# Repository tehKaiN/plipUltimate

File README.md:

# plipUltimate
plipUltimate is AVR-based device used to connect classic Amigas via Ethernet to the network. Additionally, it serves as SD card reader and includes self-updater. This project is based on [PlipBox](https://github.com/cnvogelg/plipbox).

Released under the GNU Public License V2 (see LICENSE and AUTHORS for details).

Currently IP traffic is done in bridge mode - packets are generated by Amiga's network stack and sent to interface using PLIP protocol. Since AVR CPU may run as fast as 20MHz, there is a room for improvement by moving generic packet generation to AVR. SD card reader support is yet to be added.

Both projects are released under GPLv2 license.

## Releases

See [Releases page](https://github.com/tehKaiN/plipUltimate/releases).

**Read `release notes.txt` included in release before doing anything else, otherwise you may end up very frustrated with broken pile of electronics.**

All releases consists of:

- KiCad project files: use these to generate your own gerbers,
- Gerber files: use these to order PCB from fab house,
- `amiga-sw` folder containing all prebuilt Amiga software,
- `avr-bin` folder containing prebuilt AVR .hex file,
- `changelog.txt` listing changes between releases,
- `release notes.txt` file containing important notes regarding current release.

## Assembling device

Unlike PlipBox, this project uses it's own custom PCB. Because of track pitches and vias, it is strongly advised to send Gerbers to board house.

After assembling device, you will need to program AVR with attached .hex file using on-board ISP header. Use programmer of your choice. I tend to use cheap Arduino clone as programmer (see [ArduinoISP](https://www.arduino.cc/en/Tutorial/ArduinoISP)). 

Flashing from release is done as follows:  
```
avrdude -V -p m328p -c arduino -b 19200 -PCOM3 -Uflash:w:"avr-bin\plipUltimate.hex":i -Uflash:w:"avr-bin\avr-bootloader.hex":i -Ueeprom:w:"avr-bin\plipUltimate.eep":i -U lfuse:w:"avr-bin\plipUltimate.lfs":i -U hfuse:w:"avr-bin\plipUltimate.hfs":i -U efuse:w:"avr-bin\plipUltimate.efs":i -U lock:w:"avr-bin\plipUltimate.lock":i
```
Whereas from repository:  
```
avrdude -V -p m328p -c arduino -b 19200 -PCOM3 -Uflash:w:"avr\bin\Debug\plipUltimate.hex":i -Uflash:w:"avr-bootloader\bin\Debug\avr-bootloader.hex":i -Ueeprom:w:"avr\bin\Debug\plipUltimate.eep":i -U lfuse:w:"avr\bin\Debug\plipUltimate.lfs":i -U hfuse:w:"avr\bin\Debug\plipUltimate.hfs":i -U efuse:w:"avr\bin\Debug\plipUltimate.efs":i -U lock:w:"avr\bin\Debug\plipUltimate.lock":i
```
Where `-c arduino` is your ISP type and `-PCOM3` is your ISP's COM port.

## Amiga configuration

Since Amiga software is still same as in plipBox, it's configuration steps are exactly the same. You can find details [here](https://github.com/cnvogelg/plipbox/blob/master/doc/src/amiga.md).

## Updates

plipUltimate may be updated using plipTool. Internet service providing latest update files is yet to be established.

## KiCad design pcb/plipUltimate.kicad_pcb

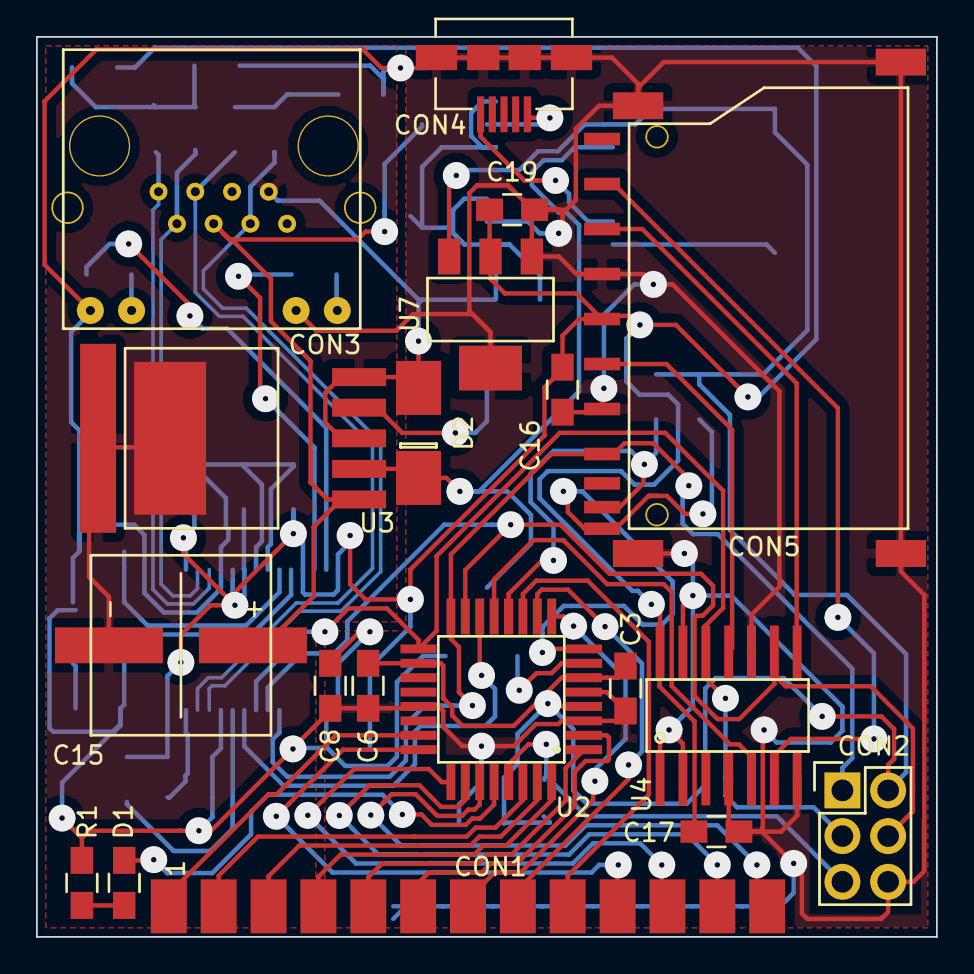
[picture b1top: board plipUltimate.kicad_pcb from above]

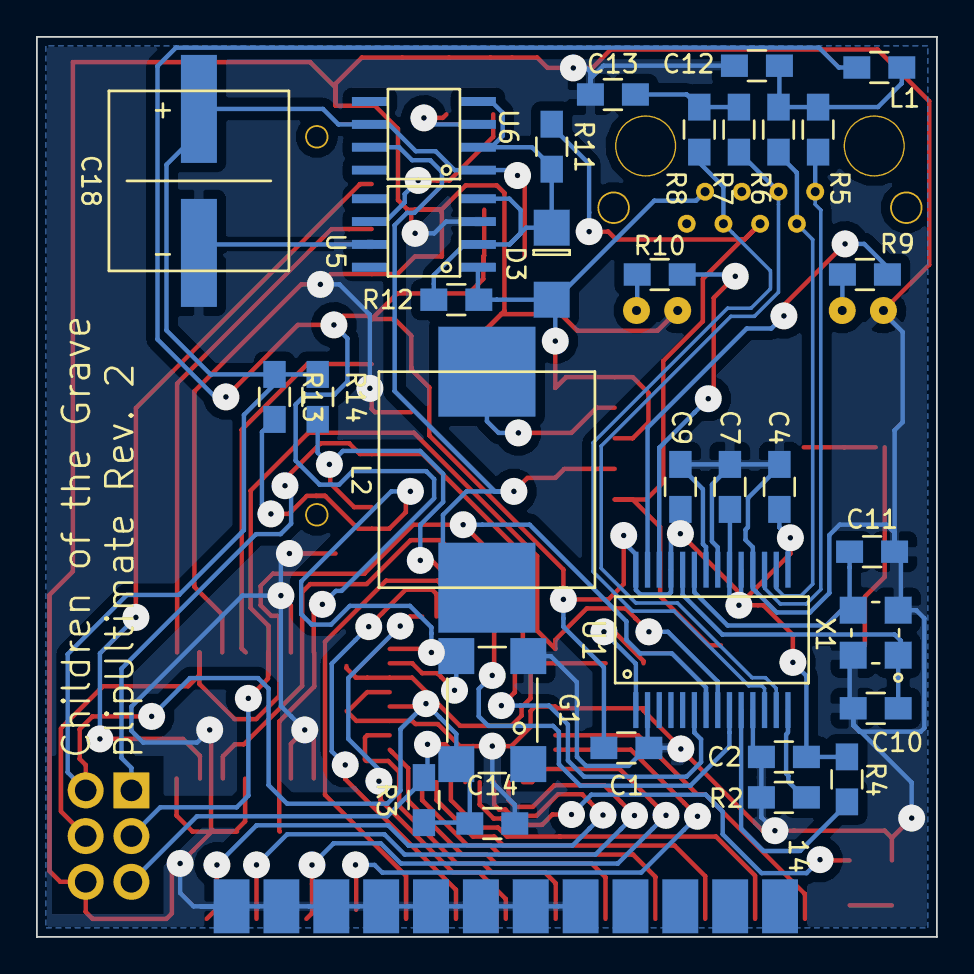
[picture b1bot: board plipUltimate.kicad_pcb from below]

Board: 2 copper layers, 50.0 x 50.0 mm, 51 parts (32 on the bottom side), 52 nets.

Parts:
C1, C2, C3, C4, C6, C7, C9, C14, C16: 100nF; 0805
C8: 10uF; 0805
C10, C11: 18pF; 0805
C12, C13, C17: 10nF; 0805
C15: 100uF 50V loESR; electrolyte_SMD
C18: 220uF 35V loESR; electrolyte_SMD
C19: 10uF 6,3V; 0805
CON1: IEEEE-1284A; d-sub25_edge
CON2: AVR-ISP-6; IDC_2x3
CON3: RJ45_C; RJ45-LEDS
CON4: USB_microB; USB-MicroB
CON5: SD_SPI; SD-SHORT
D1: YEL_LED; 0805
D2: SS34; SMA
D3: BZV55C10; SOD-80
G1: CFPS-72-20M; SMD_7050
L1: FB 100mA; 0805
L2: DE1207-100; DE-1207
R1: 820R; 0805
R2: 2k7 1%; 0805
R3, R4, R12: 10k; 0805
R5, R6, R7, R8: 49R9 1%; 0805
R9, R10: 270R; 0805
R11: 22k; 0805
R13, R14: 4k7; 0805
U1: ENC28J60; SSOP-28
U2: ATMEGA328P; TQFP-32
U3: LM2596_5.0; TO-263
U4: 74LVC125; SO-14
U5, U6: IRF7309; SO-8
U7: AMS1117_3V3; SOT-223
X1: 25MHz; XT-324

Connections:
3.3V_AVR_MOSI: CON5.2, U4.8
3.3V_AVR_SCK: CON5.5, U4.11
3.3V_SD_CS: CON5.1, U4.6
+3V3: C1.2, C2.2, C4.2, C7.2, C9.2, C16.1, C17.1, C19.1, CON5.4, L1.1, R4.1, U1.15, U1.19, U1.20, U1.25, U1.28, U4.14, U7.2
+5V: C3.1, C6.1, C14.1, C18.1, CON2.2, G1.4, R3.1, R13.1, R14.1, U2.4, U2.6, U2.18, U6.1, U6.6, U7.3
/AVR_CLK: G1.3, U2.7
/BUSY: CON1.11, U2.25
/D0: CON1.2, U2.30
/D1: CON1.3, U2.31
/D2: CON1.4, U2.32
/D3: CON1.5, U2.1
/D4: CON1.6, U2.2
/D5: CON1.7, U2.9
/D6: CON1.8, U2.10
/D7: CON1.9, U2.11
/LEDA: R9.2, U1.27
/LEDB: R10.2, U1.26
/OSC1: C11.2, U1.23, X1.3
/OSC2: C10.2, U1.24, X1.1
/POUT: CON1.12, U2.26
/RX+: CON3.3, R7.1, U1.13
/RX-: CON3.6, R8.1, U1.12
/SEL: CON1.13, U2.27
/TX+: CON3.1, R5.2, U1.17
/TX-: CON3.2, R6.2, U1.16
/~ACK: CON1.10, U2.24
/~STROBE: CON1.1, U2.23
AVR_MISO: CON2.1, CON5.7, U1.6, U2.16
AVR_MOSI: CON2.4, U1.7, U2.15, U4.9
AVR_RESET: CON2.5, R3.2, U2.29
AVR_SCK: CON2.3, U1.8, U2.17, U4.12
ETH_CS: U1.9, U2.14
GND: C1.1, C2.1, C3.2, C4.1, C6.2, C7.1, C8.1, C9.1, C10.1, C11.1, C12.1, C13.1, C14.2, C16.2, C17.2, C18.2, C19.2, CON1.18, CON1.19, CON1.20, CON1.21, CON1.22, CON1.23, CON1.24, CON1.25, CON2.6, CON3.9, CON3.11, CON4.6, CON5.3, CON5.6, CON5.12, CON5.13, G1.2, R1.2, R2.2, U1.2, U1.11, U1.18, U1.21, U1.22, U2.3, U2.5, U2.21, U4.1, U4.2, U4.4, U4.7, U4.10, U4.13, U5.3, U5.7, U7.1, X1.2
unnamed: C8.2, U1.1
unnamed: C12.2, L1.2, R5.1, R6.1
unnamed: C13.2, R7.2, R8.2
unnamed: CON3.10, R9.1
unnamed: CON3.12, R10.1
unnamed: CON4.1, U6.3
unnamed: CON4.5, U5.6
unnamed: D1.1, R1.1
unnamed: D1.2, U2.28
unnamed: D2.1, L2.2, U3.2, U6.7
unnamed: D3.1, R11.1, R12.2, U5.2, U5.4, U6.2, U6.4
unnamed: L2.1, U3.4
unnamed: R2.1, U1.14
unnamed: R4.2, U1.10
POE_0V: C15.2, CON3.7, D2.2, D3.2, R12.1, U3.3, U3.5, U5.1
POE_+24V: C15.1, CON3.4, R11.2, U3.1
SD_CS: U2.13, U4.5
SD_DETECT: CON5.10, R13.2, U2.8
SD_LOCK: CON5.11, R14.2, U2.12

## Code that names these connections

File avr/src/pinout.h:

/*
 * This file is part of PlipUltimate.
 * License: GPLv2
 * Full license: https://github.com/tehKaiN/plipUltimate/blob/master/LICENSE
 * Authors list: https://github.com/tehKaiN/plipUltimate/blob/master/AUTHORS
 */

#ifndef PINOUT_H
#define PINOUT_H

/// LED-related defines
#define LED_DDR        DDRC
#define LED_PORT       PORTC
#define LED_STATUS_PIN PC5
#define LED_STATUS     _BV(LED_STATUS_PIN)

/// Parallel status bits
#define PAR_NSTROBE_PIN PC0
#define PAR_NACK_PIN    PC1
#define PAR_BUSY_PIN    PC2
#define PAR_POUT_PIN    PC3
#define PAR_SEL_PIN     PC4

#define PAR_NSTROBE _BV(PAR_NSTROBE_PIN)
#define PAR_NACK    _BV(PAR_NACK_PIN)
#define PAR_BUSY    _BV(PAR_BUSY_PIN)
#define PAR_POUT    _BV(PAR_POUT_PIN)
#define PAR_SEL     _BV(PAR_SEL_PIN)

#define PAR_STATUS_PORT PORTC
#define PAR_STATUS_DDR DDRC
#define PAR_STATUS_PIN PINC
#define PAR_STATUS_MASK (PAR_NSTROBE | PAR_NACK | PAR_BUSY | PAR_POUT | PAR_SEL)

/// Parallel data bits
#define PAR_DATA_PORT PORTD
#define PAR_DATA_DDR DDRD
#define PAR_DATA_PIN PIND

/// SPI devices pins
#define SD_LOCK   _BV(PB0)
#define SD_CS     _BV(PB1)
#define ETH_CS    _BV(PB2)
#define SPI_MOSI  _BV(PB3)
#define SPI_MISO  _BV(PB4)
#define SPI_SCK   _BV(PB5)
// PB6 is used as XTAL1
#define SD_DETECT _BV(PB7)

#define SPI_PORT PORTB
#define SPI_PIN  PINB
#define SPI_DDR  DDRB

#endif // PINOUT_H

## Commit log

2016-05-17 Initial commit of AVR code
    Simplified IO pinout, added C::B project, removed util/delay.y
    dependency
    Reduced flash usage by 600B
2016-05-17 gitIgnore changes
    .hex should be now accessible
2016-05-17 Added global pinout config, introduced SPI SD card support
2016-05-17 file reorganization, added spi support for card reader
2016-05-17 converted to stdint.h types, minor fixes
2016-05-17 added PCB KiCad project
2016-05-18 Minor KiCad schematic fixes
    Tweaked resistor symbol, added SD decoupling, changed module layout on
    page
2016-05-19 Added d-sub 25 edge connector footprint
2016-05-19 Added hand solder footprints, MOSFET gate powered by zener regulator
2016-05-20 Decoupling for 7407, minor schematic tweaks
    most parts are associated with footprints, added more of them
2016-05-21 All footprints done!
2016-05-21 Laid out power circuit
2016-05-22 Changed eth crystal to 3-pin SMD, all parts are aligned on board now
2016-05-22 further layout work - 25 connections to go
2016-05-24 everything routed!
    TODO: home-etching optimizations
2016-05-26 Revised schematic, reroute in progress
2016-05-30 Complete rev 2 sch and PCB
2016-05-30 minor pcb fixes
    TODO: 20MHz & SD footprints are broken
2016-05-31 further layout optimizations
2016-05-31 minor layout tweaks
2016-06-01 Rev 2.1, associated footprints with 3D models
    This release is not suitable for home etching
2016-06-02 UART comm removal
2016-06-02 beginning of UART message analysis
    first step in replacing UART comm with parallel comm
2016-12-16 Added blinker test program
2016-12-19 Bootloader stub
2016-12-20 kicad project minor changes
2016-12-20 Some fixes for 20MHz. Further code documenting.
2016-12-23 Documented eth.h inline fns and magic packet-related code
2016-12-23 Removed excessive cli() before wdt_disable, minor comments
2016-12-23 First step to remove PIO HAL
2016-12-23 PIO HAL removal part 2
2016-12-23 Better comments in bridge main loop, documented pio_util a bit
2016-12-24 Removed par_low files, moved code to related fns
    12 bytes less, woo!
2016-12-24 Documented util.h a bit, minor changes in argument types
2016-12-24 Simplified data buffer access, pb_proto fn names refactor
2016-12-25 Refactored timer code.
    Should be now clock-independent, also revealed some problems regarding kbps calc
2016-12-26 Added utilReset() fn
2016-12-26 Amiga command interface stub
    Although reset command should now work in bridge mode
2016-12-26 Renamed stack checking function to more intuitive name
2016-12-26 Added status led support
2016-12-28 Added plipTool, made device resettable from it, proper wdt fns
    added no enc28j60 mode for debugging purposes
2017-01-05 ACK state reading for plipTool
2017-01-10 Renamed param type & struct to tConfig and g_sConfig respectively
2017-01-10 Added gitignore to KiCad part
2017-01-10 CMD_GETCONFIG implemented, not tested
2017-01-10 Removed c::b .layout files
2017-01-10 Added c::b .layout file to .gitignore
2017-01-11 initial plipTool "getConfig" cmd support, not tested
2017-01-17 Fixed erroreous LED_PIN use
2017-01-17 c::b .gitignore update
2017-01-17 fixed cmd /ACK release
2017-01-17 renamed bridge.c's flags global
2017-01-17 Prolonged /ACK pulse to 20ms, fixed plipTool CIA int handling
    plipTool now receives data from plipUltimate, albeit wrong.
2017-01-17 Added proper build version, typo fix in getconfig ip display
2017-01-17 Fixed recv errors
2017-01-17 Remove not needed comment
    ACK prolonging was required for proper int detection, making it shorter won't make a difference in anything.
2017-01-17 Reorganized plipTool source
2017-01-17 plipTool's config update now works
2017-01-18 Added SPM to bootloader, not tested yet
2017-01-18 Updated bootloader's c::b project file
2017-01-19 Added hex2puf util
    Works on windows, on Amiga it doesn't - buggy VBCC std lib?
2017-01-19 Added hex2puf test files to .gitignore
2017-01-19 Cleaned up hex2puf source a bit
2017-01-19 Fixed hex2puf on m68k
    Crashes were stack-related. Changed big allocs to heap.
2017-01-19 added plipTool test files to .gitIgnore
2017-01-19 Added flashing code to plipTool, not tested yet
2017-01-21 bootloader's PAR_DATA_PIN doesn't work, wtf
2017-01-21 Bootloader now flashes Ami properly
2017-01-23 Refactored & reorganized code a bit - removed test modes & UART dump fns
2017-01-23 Merged pb_util.c with pb_proto.c
2017-01-23 Removed UART verbose mode
2017-01-23 Removed avr-blink program, updated GPLv2 notice in all files
2017-01-24 Removed old build version defines and unused pio_util_handle_ fns
2017-01-25 Added missing comment to bootloader code
2017-01-25 Renamed param fns to config
2017-01-25 Renamed param.c and .h to config.c and .h
2017-01-25 Updated remaining GPL notices
2017-01-25 Refactored SPI fn names
2017-01-25 ENC28J60 activity indicator - LED is dimmed if disabled
2017-01-26 proper README.md
2017-01-26 minor changes regarding SD state, added self updater note.
2017-01-26 Added ISP avrdude commands
2017-01-26 fixed typo
2017-01-26 Updated license notices, prob'ly for last time
2017-01-26 changed copyright notice
2017-02-04 unified passive component values
2017-02-04 updated schematic meta table
2017-02-05 Updated pcb meta table
2017-12-11 Added rev2.1 instructions
2017-12-11 removed gerbers & binaries
2017-12-13 Reorganized code, main code is built using makefile
2017-12-13 bin is now ignored
2017-12-13 Added missing extern
2017-12-13 Removed plipbox makefile, made main makefile self-aware
2017-12-13 Added bootloader makefile
2017-12-13 removed garbage
2017-12-13 Added pliptool makefile
2017-12-13 Removed old code::blocks project files
